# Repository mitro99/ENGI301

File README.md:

# ENGI301
Repository for ENGI 301 coursework

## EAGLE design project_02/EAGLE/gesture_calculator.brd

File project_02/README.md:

### No Touch Gesture Calculator

Hackster Project can be found at https://www.hackster.io/andrei-mitrofan/no-touch-gesture-calculator-40e7d4

##Story

I work in a research lab and taking my gloves off just to do some basic arithmetic on my phone has always seemed very inefficient and kind of annoying to do, since once you take gloves off it's a nightmare to put them back on immediately afterward. Therefore, I designed this gesture calculator that allows me to do all those basic calculations without having to take my gloves off or worry about contaminating my phone. I've also wanted to dive into tinyML for a while now, so this felt like an appropriate project on which to implement my first TFLite project on the PocketBeagle.

##PCB Design

I have created a PCB for the project in order to minimize its size and make it more comfortable to be used as an actual wearable. This repository contains all the files necessary for manufacturing the board.:

-"docs" contains the original project proposal, as well as PDF files of the schematic, top and bottom of the actual PCB, and the bill of materials.

-"EAGLE" contains all the EAGLE file, including the library with all the components used, the schematic, the board, and the design rules.

-"mfg" contains all the manufacturing files, most notably the Gerber files.

##Operation Instructions

The device is set up to run the inference code upon boot, so you just need to plug in the PocketBeagle and, after waiting for a couple of minutes, it should be up and ready to predict gestures. The flow of the calculator is as follows:

-Draw out the first number in the air

-Flick your wrist (this advances the calculator to the operator selector)

-Draw out a digit 1 - 5 to select the operator you want

-Draw out the second number in the air

-Flick your wrist again to calculate the result

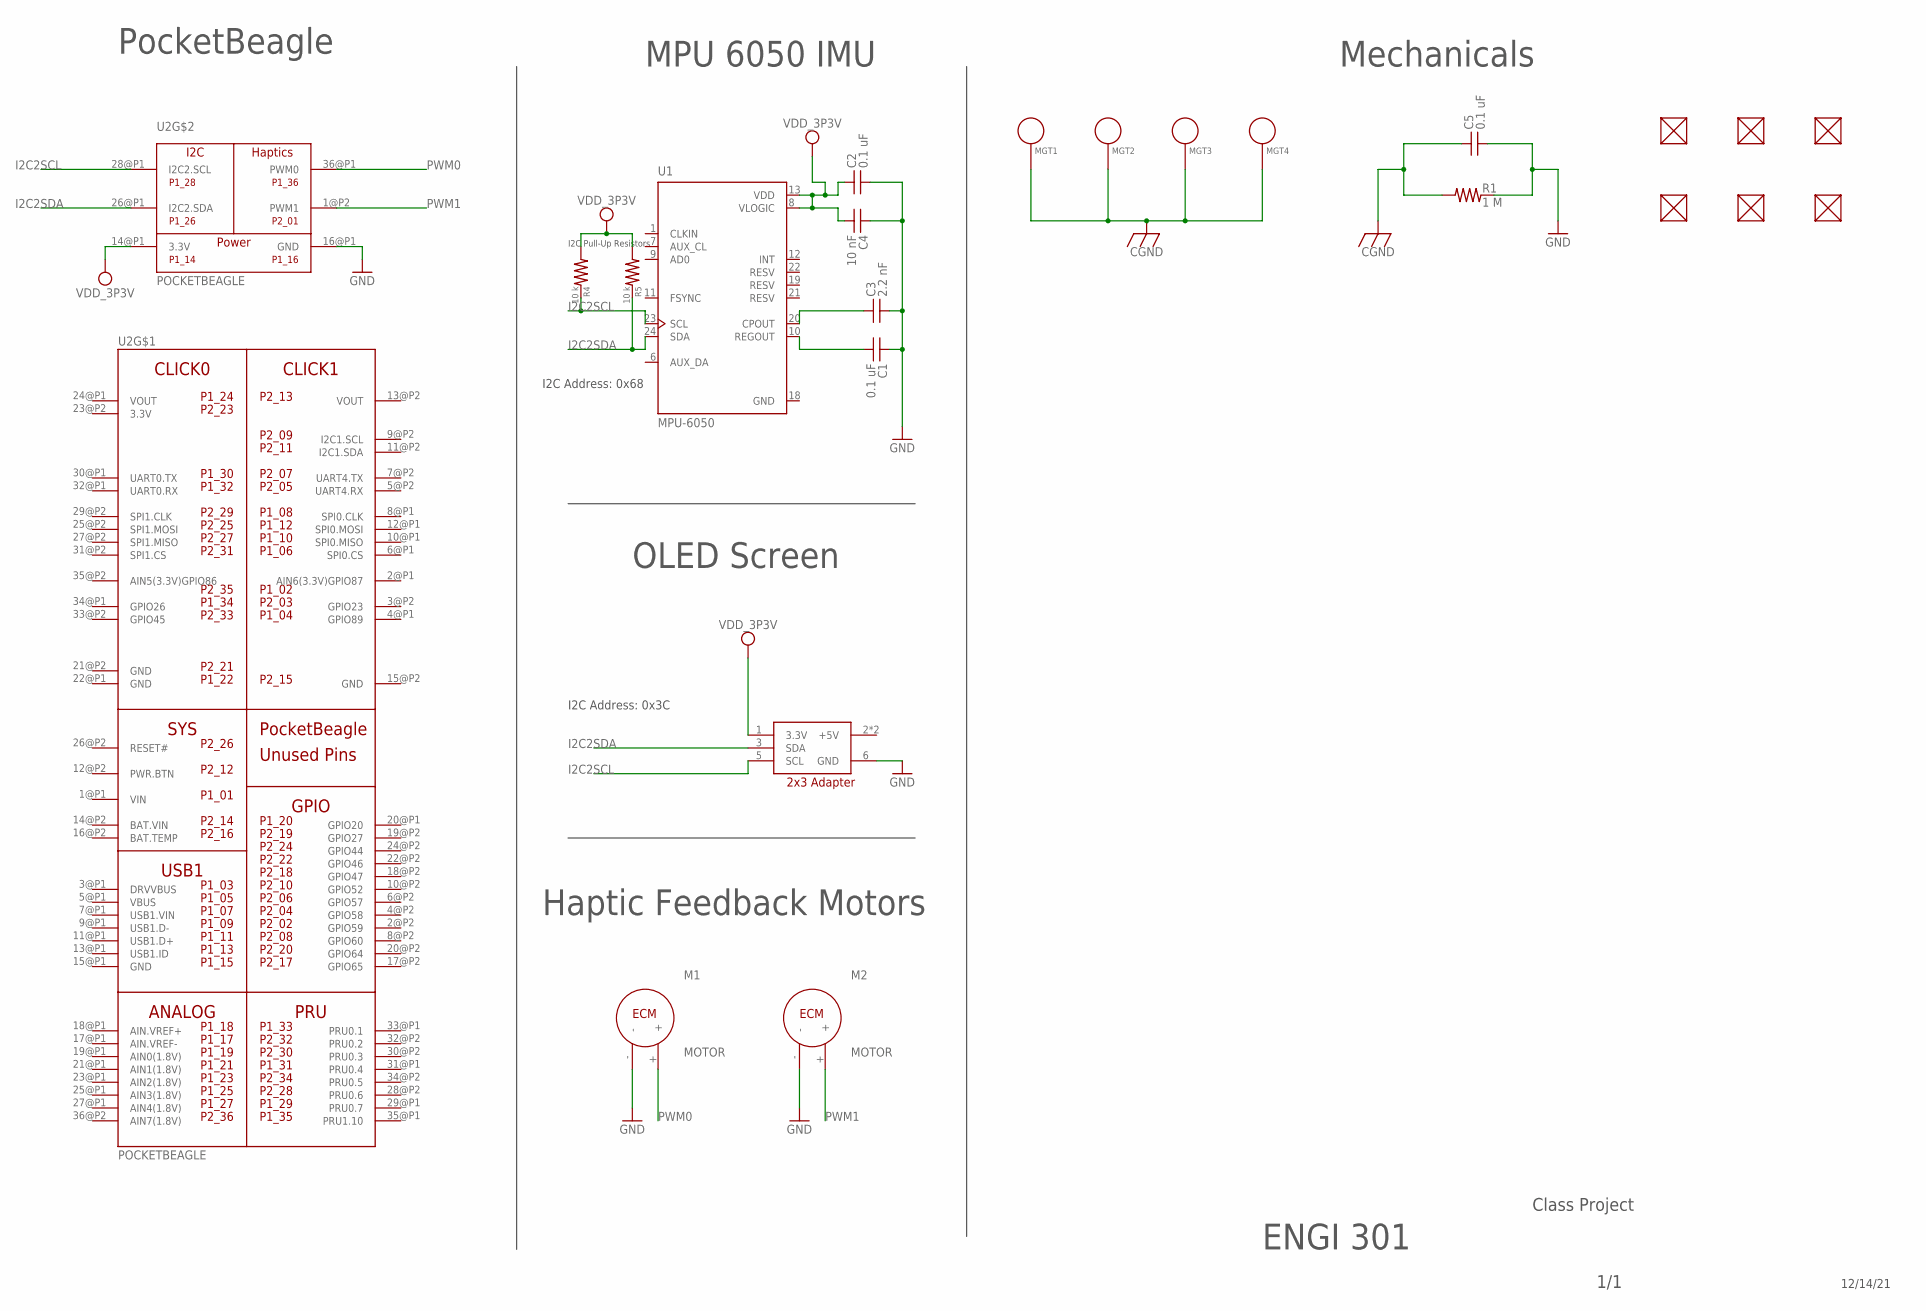
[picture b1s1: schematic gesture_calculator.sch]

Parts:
C1, C2, C5: 0.1 uF; 0603
C3: 2.2 nF; 0603
C4: 10 nF; 0603
FUD1, FUD2, FUD3, FUD4, FUD5, FUD6: FIDUCIAL; FIDUCIAL_40MIL
M1, M2: MOTOR
MGT1, MGT2, MGT3, MGT4: MOUNTING_HOLE
R1: 1 M; 0603
R4, R5: 10 k; 0603
RPI1: ADAPTER_2X3_THM; RASPBERRYPI_2X3
U1: MPU-6050; QFN50P400X400X95-24N
U2: POCKETBEAGLE

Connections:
3.3V: U2.23@P2 (3.3V)
BAT.VIN: U2.14@P2 (BAT.VIN)
CGND: C5.1, MGT1.P$1, MGT2.P$1, MGT3.P$1, MGT4.P$1, R1.1
GND: C1.1, C2.2, C3.2, C4.1, C5.2, M1.-, M2.-, R1.2, RPI1.6 (GND), U1.18 (GND), U2.15@P2 (GND), U2.16@P1 (GND), U2.21@P2 (GND), U2.22@P1 (GND)
I2C2SCL: R4.2, RPI1.5 (SCL), U1.23 (SCL), U2.28@P1 (I2C2.SCL)
I2C2SDA: R5.2, RPI1.3 (SDA), U1.24 (SDA), U2.26@P1 (I2C2.SDA)
unnamed: C1.2, U1.10 (REGOUT)
unnamed: C3.1, U1.20 (CPOUT)
PWM0: M1.+, U2.36@P1 (PWM0)
PWM1: M2.+, U2.1@P2 (PWM1)
VDD_3P3V: C2.1, C4.2, R4.1, R5.1, RPI1.1 (3.3V), U1.8 (VLOGIC), U1.13 (VDD), U2.14@P1 (3.3V)
VIN: U2.1@P1 (VIN)
VOUT: U2.13@P2 (VOUT), U2.24@P1 (VOUT)

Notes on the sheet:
PocketBeagle
Haptic Feedback Motors
MPU 6050 IMU
OLED Screen
Mechanicals
ENGI 301
Class Project
1/1
12/14/21
I2C Pull-Up Resistors
I2C Address: 0x3C
I2C Address: 0x68

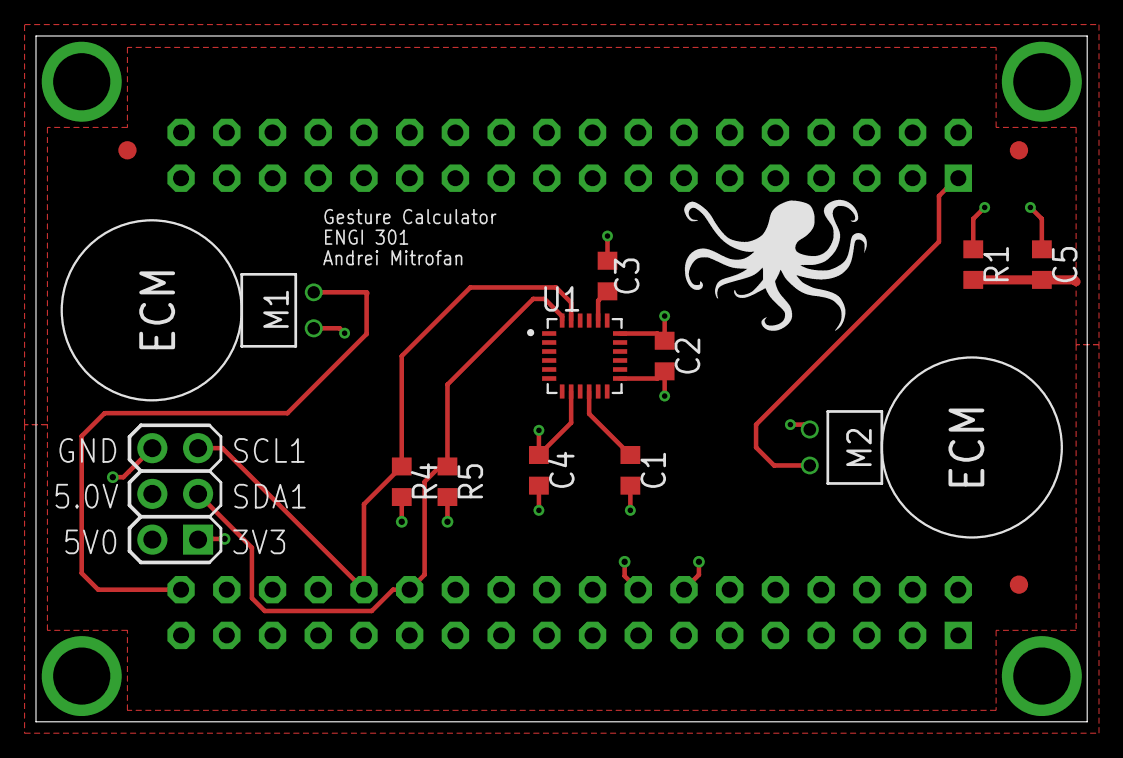
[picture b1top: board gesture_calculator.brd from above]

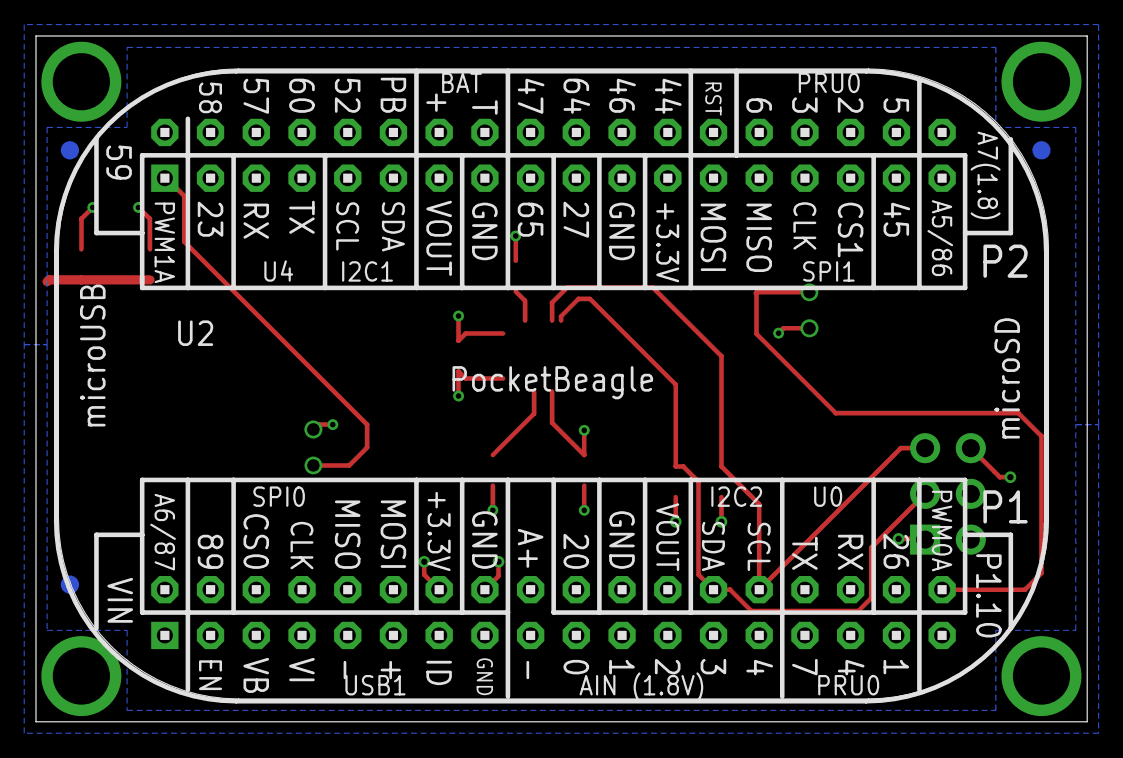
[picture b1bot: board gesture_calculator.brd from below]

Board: 4 copper layers, 58.4 x 38.1 mm, 23 parts (4 on the bottom side), 10 nets.

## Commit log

2021-09-17 Created temporary experiment for class
2021-10-05 Added assignment 4
2021-10-05 Adding assignment 3
2021-10-08 Starting testing of MPU6050
2021-10-14 Added project proposal
2021-10-14 Adding acquisition testing
2021-10-14 Added acquisition
2021-10-14 Fix conflict
2021-10-14 Reorganized files
2021-10-14 data collection
2021-10-14 Gesture testing
2021-10-14 Add data visualization notebook
2021-10-14 Adding testing data 1-4
2021-10-14 Updated sensor range
2021-10-14 'Added images of 1-4 digits sensor values'
2021-10-15 New testing data
2021-10-15 Added 25 samples
2021-10-16 Adding test files for 0-4
2021-10-17 Added test data for 5-9
2021-10-18 Added 25 more samples for each number
2021-10-18 Added testing notebook
2021-10-18 'Updated hyperparameter search'
2021-10-21 Updated Training Code for wavelet transform
2021-10-21 Finalized parameter optimization
    Finished optimizing learning network, got conversion to lite model for pocketbeagle
2021-10-21 Added parameters for prediction
2021-10-22 Added processing of gesture data
2021-10-22 Made Model Smaller
2021-10-22 Changed interpreter to non-signature based
2021-10-23 Tried outdated tf
2021-10-27 Changed split type to ensure consistency
2021-10-27 Added full combo lock
2021-10-27 Added extra model
2021-10-28 Cleaned up predict code
2021-10-28 Duplicated file
2021-10-28 Cleaned up prediction
2021-10-31 Adding data after casing
2021-10-31 new data
2021-10-31 more data
2021-10-31 Renamed files
2021-10-31 Added 50 trials for every gesture
2021-10-31 Updated training for new data
2021-10-31 Added normal data
2021-10-31 Chanes
2021-11-01 Added logic for code and calculator function
2021-11-09 Readded acquisition
2021-11-09 Added comments
2021-11-09 Finalize comments
2021-11-09 Finalized comments
2021-11-09 Deleted extras
2021-11-09 Added ReadMe
2021-11-17 Added PCB proposal number 2
2021-11-17 Created project 2 folder
2021-12-15 Added PCB and manufacturing files
2021-12-15 Moved things around
